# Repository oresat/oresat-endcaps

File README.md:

# "End Cap" PCBs for OreSat

These are the "end cap" PCBs that attach to the +Z and -Z ends of the satellites. Mostly these are to protect the end cards from "space", as well as to hold the magnetometers (two per end cap) as far as away from ferrous stuff as possible. It's also a good place for backup antennas, specifically patch antennas (S band and GPS L1).

## Features

- Cutouts for deployable antennas
- Double magnetometers.
- Single vertical 10mm tall 1.27 mm connector that plugs into the "end card" card.
    - On the End Cap:  Harwin M55-6001242R 12 pin female vertical connector 
    - On the End Card below: Harwin M55-7011242R 12 pin male vertical connector
- No available RF connectors.

## LICENSE

Copyright the Portland State Aerospace Society, 2024.

This source describes Open Hardware that is licensed under CERN-OHL-S v2, or any later version.

You may redistribute and modify this source and make products using it under the terms of the CERN-OHL-S v2 (https://ohwr.org/cern_ohl_s_v2.txt).

This source is distributed WITHOUT ANY EXPRESS OR IMPLIED WARRANTY, INCLUDING OF MERCHANTABILITY, SATISFACTORY QUALITY AND FITNESS FOR A PARTICULAR PURPOSE. Please see the CERN-OHL-S v2 for applicable conditions.

Source location: <https://github.com/oresat/>

As per CERN-OHL-S v2 section 4, should You produce hardware based on this source, You must where practicable maintain the Source Location visible on the external case of the Gizmo or other products you make using this source.

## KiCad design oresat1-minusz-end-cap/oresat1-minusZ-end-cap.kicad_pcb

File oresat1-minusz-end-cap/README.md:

---
title: "**OreSat1 -Z End Cap**"
subtitle: |
  **Fabrication and Assembly Information**\
  For build TIME-STAMP
fontsize: 10pt
geometry:
  - margin=0.5in
toc: true
toc-depth: 2
colorlinks: true
urlcolor: blue
---

\newpage

# About this Board

## Board Description

The OreSat1 -Z End Cap is the board that "caps" the -Z end of the OreSat1 satellite. It protects the -Z End Card and also carries two PNI RM3100 magnetometers, as far away from the internal OreSat magnetic noise as possible. 

## Documentation Links

- End cap hardware Git repository: <https://github.com/oresat/oresat-endcap>
- **TODO:** End Cap Design Notes + Design Review Notes

## Documentation Files

| Filename                        | Notes                                    |
| ------------------------------- | ---------------------------------------- |
| README.pdf                      | This README file                         |
| PROJECT-NAME-outline.dxf        | Board outline (with holes) in DXF format |
| PROJECT-NAME-pcba.step          | 3D model of PCBA (with components)       |
| PROJECT-NAME-render-bot.jpg     | Render of the top of the 3D model        |
| PROJECT-NAME-render-bot.jpg     | Render of the bottom of the 3D model     |
| PROJECT-NAME-schematic.pdf      | PDF of board schematics                  |

## Contact Information

- Website: <https://www.oresat.org/>
- Email: <oresat@pdx.edu>
- Instagram: @pdxaerospace

## Board Renders

{width=50%}
{width=50%}

\newpage

# Printed Circuit Board (PCB) Fabrication Information

## Board Info

- 4 layer board
- Bounding box is 105.6 x 105.6 mm
- Board thickness is 1.59 mm (0.063 inch)

## Board Requirements

- Design Rules
    - Minimum Trace / Space design rules
       - Outer layers: 0.127 mm (5.0 mil) / 0.127 mm (5.0 mil)
       - Inner layers: 0.127 mm (5.0 mil) / 0.127 mm (5.0 mil)
    - Outer dimension router tolerance: +/- 0.254 mm (10.0 mil)
    - Hole placement tolerance: +/- 0.075 mm (3.0 mil)
    - Inner tab routed slot tolerance: +/- 0.254 mm (10.0 mil)
- Drills
   - Drill Positional Tolerance: 0.051 mm (2.0 mil)
   - Drill Size tolerance: +/- 0.064 mm (2.5 mil)
- Plated/Un-plated holes
  - There are 11 un-plated (NPT) holes
  - PTH minimum diameter: 0.254 mm (10 mil)
  - PTH minimum annulus: 0.102 mm (4 mil) radius
- Outline/Routing
  - Requires a 1.0 mm or smaller diameter routing bit
- Slots
  - There are no slots.
- Cutouts
  - There is one cutout.
- There are 3 fiducials on the top layer and 3 fiducials on the bottom layer.
- Panel tabs ("mouse bites")
   - Card edges must be smooth; no mouse bites or other intrusions into the card outline.
   - If external mouse bites are required, minimize and customer will remove by hand before assembly.
- If not otherwise specified, build to IPC 6012 Class 2 or better.

## Materials

- No controlled impedance.
- Outer layers must be 1 oz Copper, inner layers can be 0.5 or 1.0 oz Copper.
- Isola FR408HR or material recommended.
- Board Surface treatment should be ENIG, althogh immersion Silver is acceptable.
- White silkscreen on top and bottom surface
- Taiyo PSR-4000 or equivalent soldermask on top and bottom, no requirements for color.

## Suggested Stack Up

| Layer         | Thickness           | Notes                                        |
|---------------|---------------------|----------------------------------------------|
| Top Copper    | 0.043 mm /  1.7 mil |  Layer 1 foil, 1 oz Cu after plating         |
| prepreg       | 0.200 mm /  7.9 mil |  Prepreg - Isola FR408HR 2113                |
| Layer 2       | 0.018 mm /  0.7 mil |  Layer 2 foil, 0.5 oz Cu                     |
| Core          | 0.991 mm /   39 mil |  Core Isola FR408HR                          |
| Layer 3       | 0.018 mm /  0.7 mil |  Layer 3 foil, 0.5 oz Cu                     |
| prepreg       | 0.200 mm /  7.9 mil |  Prepreg - Isola FR408HR 2113                |
| Bottom Copper | 0.043 mm /  1.7 mil |  Layer 4 foil, 1 oz copper after plating     |
| **Total Stackup** | **1.588 mm / 62.5 mil** |                                      |

## Array / Panel Information

- Coordinate with Contract Manufacturer (CM) for optimal size of this panel.
- If no feedback from CM, then produce single boards (no panel).

## Fabrication Files

### IPC-2581 File

| Filename                 | Notes                                   |
| ------------------------ | --------------------------------------- |
| PROJECT-NAME-ipc2581.xml | IPC-2581 board information file         |

### Legacy PCB Files

| Filename                      | Notes                                         |
| ------------------------------| --------------------------------------------- |
| PROJECT-NAME-Edge_Cuts.gbr    | RS274X file for the dimension (outline) layer |
| PROJECT-NAME-F_Silkscreen.gbr | RS274X file for the top silkscreen            |
| PROJECT-NAME-F_Mask.gbr       | RS274X file for the top soldermask            |
| PROJECT-NAME-F_Cu.gbr         | RS274X file for the top copper layer          |
| PROJECT-NAME-In1_Cu.gbr       | RS274X file for the layer 2 copper            |
| PROJECT-NAME-In2_Cu.gbr       | RS274X file for the layer 3 copper            |
| PROJECT-NAME-B_Cu.gbr         | RS274X file for the bottom copper layer       |
| PROJECT-NAME-B_Mask.gbr       | RS274X file for the bottom soldermask         |
| PROJECT-NAME-B_Silkscreen.gbr | RS274X file for the bottom silkscreen         |
| PROJECT-NAME-NPTH.drl         | Excellon file for non-plated through holes    |
| PROJECT-NAME-PTH.drl          | Excellon file for plated through holes        | 

\newpage

# Printed Circuit Board Assembly (PCBA) Information

## Assembly Info

- There are components on the top and bottom side of the board.
- This PCBA is mostly surface mount (SMT).

## Assembly Requirements

- Assemble to IPC Class 2 or better
- Bake components that are not moisture sealed to appropriate levels as required.
- Solder paste MUST be leaded.
- Aqueous flux and wash strongly preferred.
   - Clean to NASA Standard "Visibly Clean (VC)": No particles or residues are visible to the naked eye.
- No conformal coating.
- Ship in antistatic protective bag

## Component Specific Assembly Information

- No specific requirements.

## Assembly Files

### IPC-2581 File

| Filename                 | Notes                           |
| ------------------------ | ------------------------------- |
| PROJECT-NAME-ipc2581.xml | IPC-2581 board information file |

### Bill of Materials (BOM)

| Filename             | Description                            |
| -------------------- | -------------------------------------- |
| PROJECT-NAME-bom.csv | BOM in Comma Separated Variable format |

### Solder Paste Stencils

| Filename                 | Notes                                            |
| ------------------------ | ------------------------------------------------ |
| PROJECT-NAME-B_Paste.gbr | RS274X file for top/front solder paste stencil   |
| PROJECT-NAME-F_Paste.gbr | RS274X file for bottom/back solder paste stencil |

### Mounting/Placement Location

| Filename            | Description                                 |
| ------------------- | ------------------------------------------- |
| PROJECT-NAME-3u.pos | Pick and place locations for components     |

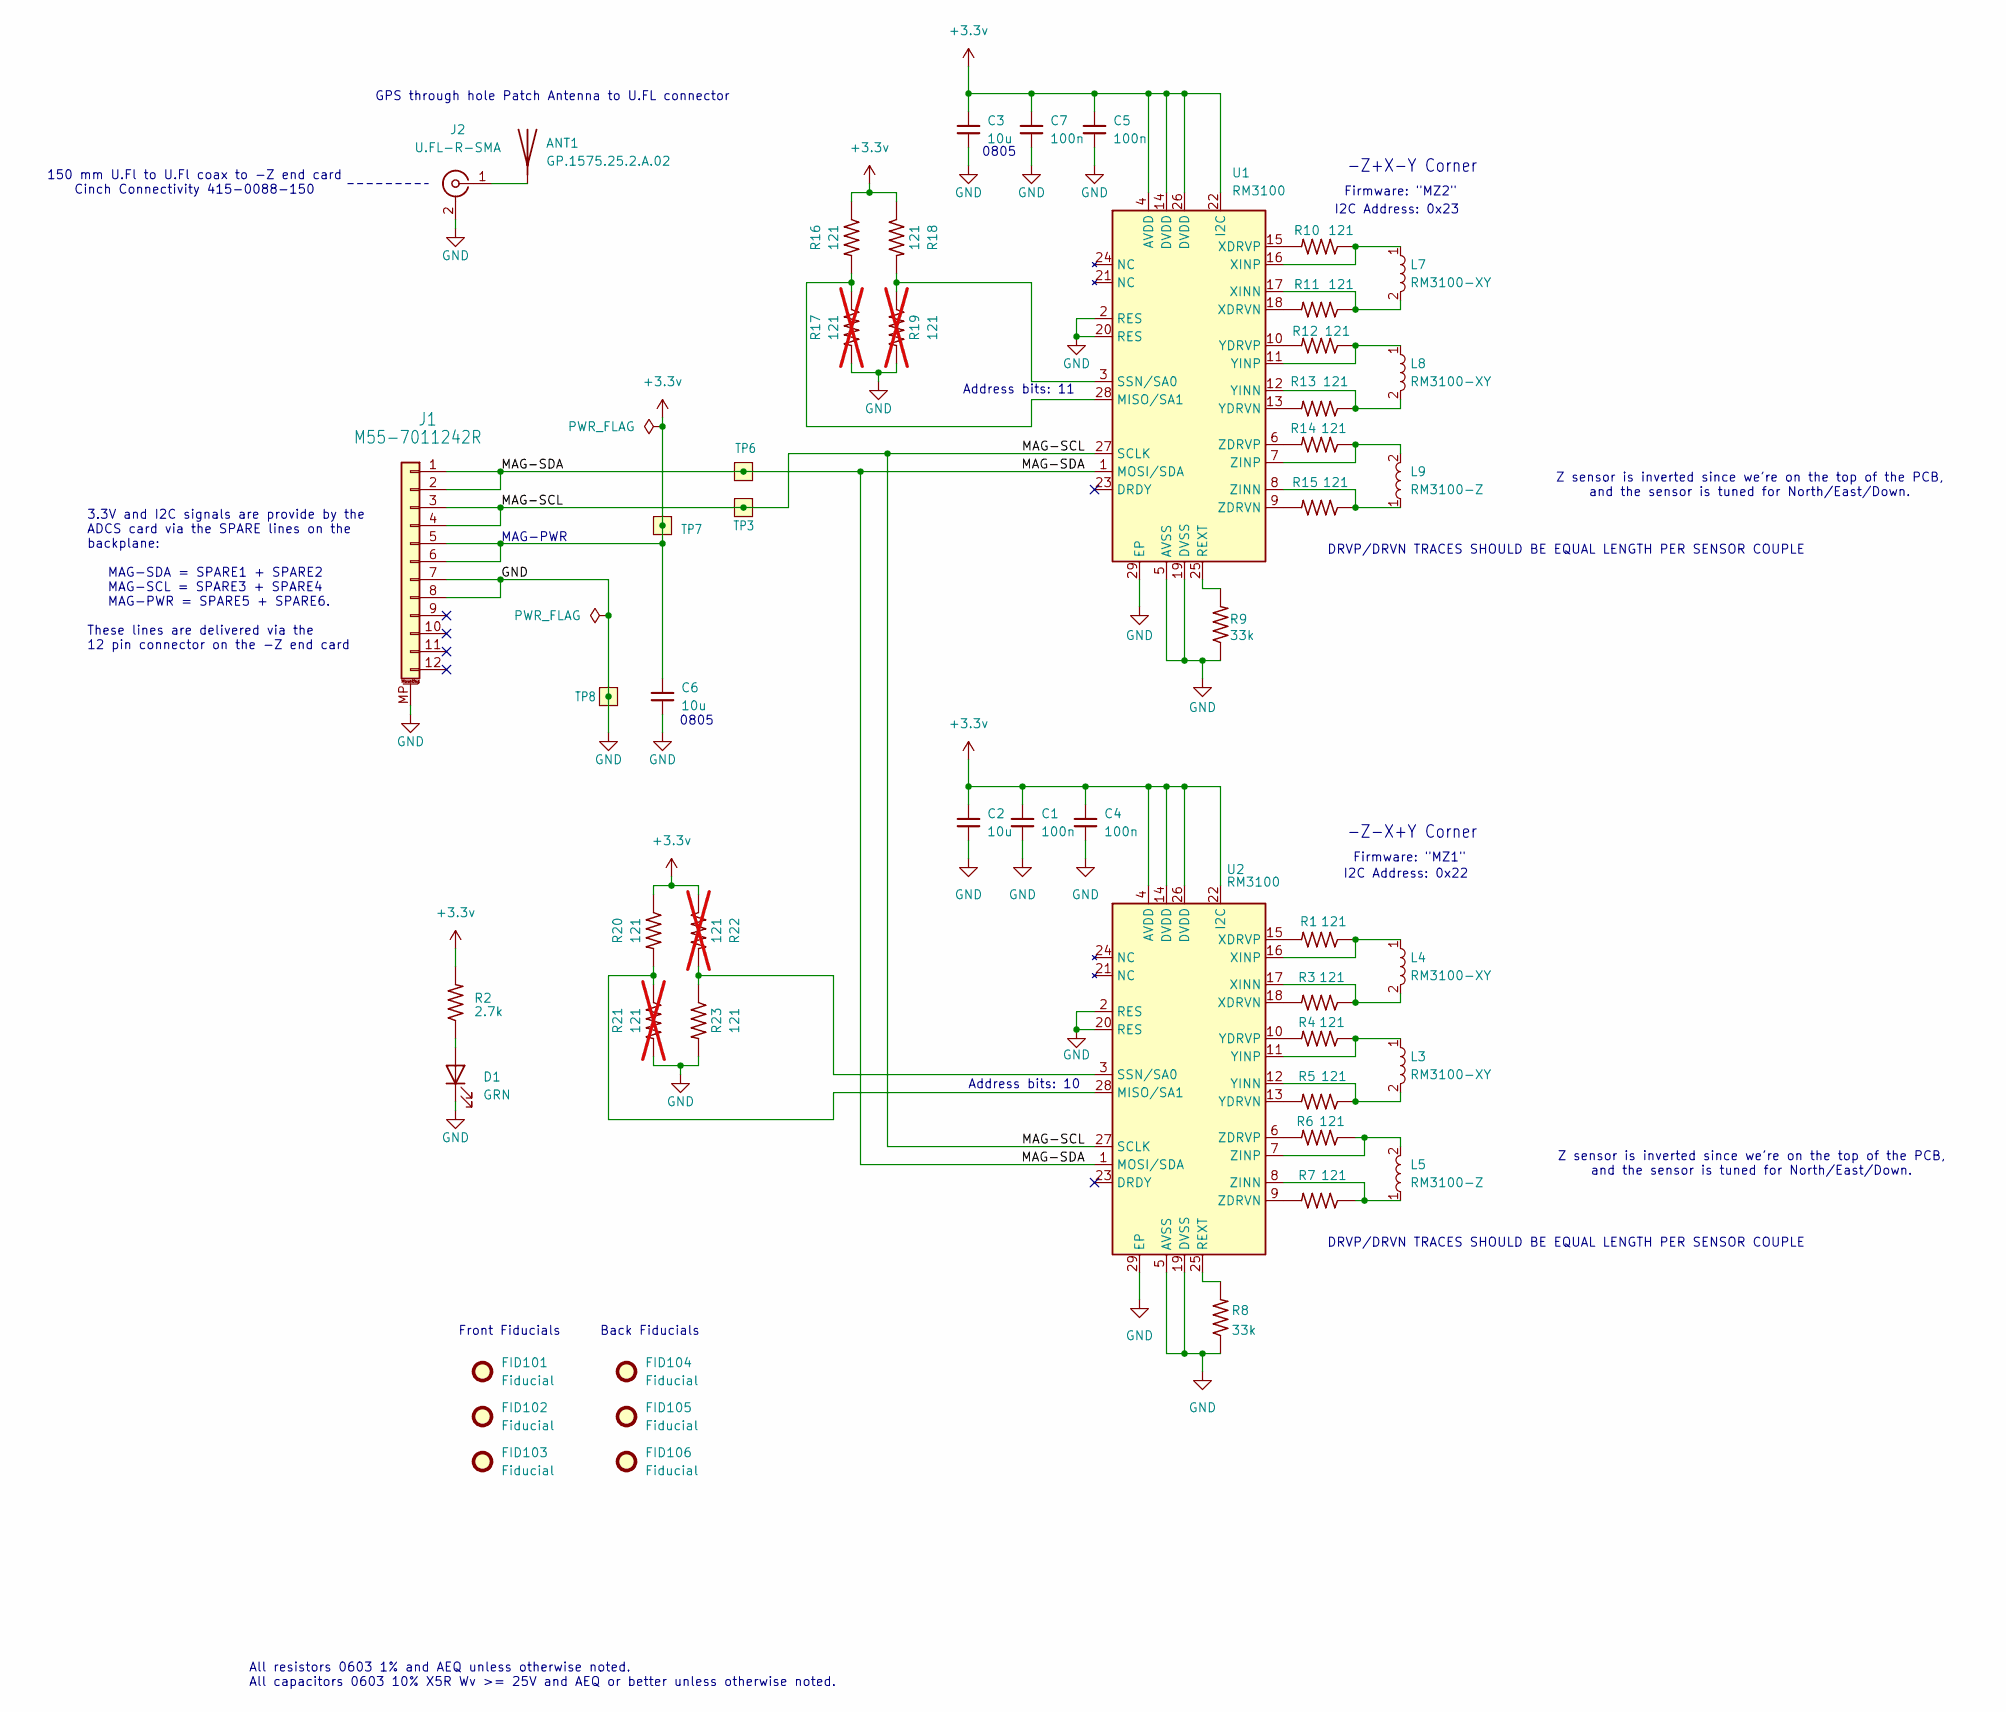
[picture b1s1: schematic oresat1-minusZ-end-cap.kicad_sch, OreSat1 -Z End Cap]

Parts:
ANT1: GP.1575.25.2.A.02; Taoglas-GPS-Patch-Antenna; MPN GP.1575.25.2.A.02
C1, C4, C5, C7: 100n; 0603-C-NOSILK; MPN C0603C104K5RACAUTO
C2, C3, C6: 10u; 0805-C-NOSILK; MPN GRT21BC71E106KE13K
D1: GRN; 0603-C-NOSILK; MPN 150060GS75000
FID101, FID102, FID103, FID104, FID105, FID106: Fiducial; Fiducial_1mm_Mask2mm
J1: M55-7011242R; J-Harwin-M55-7XX1242R; MPN M55-7011242R
J2: U.FL-R-SMA; U.FL_Hirose_U.FL-R-SMT-1_Vertical; MPN U.FL-R-SMT-1(10)
L3, L4, L7, L8: RM3100-XY; RM3100 SEN-XY-f; MFR PNI Sensors
L5, L9: RM3100-Z; RM3100 SEN-Z-f; MFR PNI Sensors
R1, R3, R4, R5, R6, R7, R10, R11, R12, R13, R14, R15, R16, R18, R20, R23: 121; 0603-C-NOSILK; MPN RMCF0603FT121R
R2: 2.7k; 0603-C-NOSILK; MPN RMCF0603FT2K70
R8, R9: 33k; 0603-C-NOSILK; MPN RMCF0603FT33K0
R17, R19, R21, R22: 121; 0603-C-NOSILK; MPN RMCF0603FT121R; not fitted
TP3, TP6, TP7, TP8: Test-Point; TestPoint-0.75mm-th; MPN N/A
U1, U2: RM3100; U-PNI-RM3100-IC; MFR PNI Sensors

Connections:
+3.3v: C1.1, C2.1, C3.1, C4.1, C5.1, C6.1, C7.1, J1.5, J1.6, R2.2, R16.1, R18.1, R20.1, R22.1, TP7.1 (1_1), U1.4 (AVDD), U1.14 (DVDD), U1.22 (I2C), U1.26 (DVDD), U2.4 (AVDD), U2.14 (DVDD), U2.22 (I2C), U2.26 (DVDD)
/MAG-SCL: J1.3, J1.4, TP3.1 (1_1), U1.27 (SCLK), U2.27 (SCLK)
/MAG-SDA: J1.1, J1.2, TP6.1 (1_1), U1.1 (MOSI/SDA), U2.1 (MOSI/SDA)
GND: C1.2, C2.2, C3.2, C4.2, C5.2, C6.2, C7.2, D1.1 (K), J1.7, J1.8, J1.MP (MountPin), J2.2 (Ext), R8.1, R9.1, R17.2, R19.2, R21.2, R23.2, TP8.1 (1_1), U1.2 (RES), U1.5 (AVSS), U1.19 (DVSS), U1.20 (RES), U1.29 (EP), U2.2 (RES), U2.5 (AVSS), U2.19 (DVSS), U2.20 (RES), U2.29 (EP)
unnamed: ANT1.1 (A_1), J2.1 (In)
unnamed: D1.2 (A), R2.1
unnamed: R16.2, R17.1, U1.28 (MISO/SA1)
unnamed: R9.2, U1.25 (REXT)
unnamed: R18.2, R19.1, U1.3 (SSN/SA0)
unnamed: R11.2, U1.18 (XDRVN)
unnamed: R10.2, U1.15 (XDRVP)
unnamed: L7.2, R11.1, U1.17 (XINN)
unnamed: L7.1, R10.1, U1.16 (XINP)
unnamed: R13.2, U1.13 (YDRVN)
unnamed: R12.2, U1.10 (YDRVP)
unnamed: L8.2, R13.1, U1.12 (YINN)
unnamed: L8.1, R12.1, U1.11 (YINP)
unnamed: R15.2, U1.9 (ZDRVN)
unnamed: R14.2, U1.6 (ZDRVP)
unnamed: L9.1, R15.1, U1.8 (ZINN)
unnamed: L9.2, R14.1, U1.7 (ZINP)
unnamed: R20.2, R21.1, U2.28 (MISO/SA1)
unnamed: R8.2, U2.25 (REXT)
unnamed: R22.2, R23.1, U2.3 (SSN/SA0)
unnamed: R3.2, U2.18 (XDRVN)
unnamed: R1.2, U2.15 (XDRVP)
unnamed: L4.2, R3.1, U2.17 (XINN)
unnamed: L4.1, R1.1, U2.16 (XINP)
unnamed: R5.2, U2.13 (YDRVN)
unnamed: R4.2, U2.10 (YDRVP)
unnamed: L3.2, R5.1, U2.12 (YINN)
unnamed: L3.1, R4.1, U2.11 (YINP)
unnamed: R7.2, U2.9 (ZDRVN)
unnamed: R6.2, U2.6 (ZDRVP)
unnamed: L5.1, R7.1, U2.8 (ZINN)
unnamed: L5.2, R6.1, U2.7 (ZINP)

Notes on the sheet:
Back Fiducials
0805
GPS through hole Patch Antenna to U.FL connector
Firmware: "MZ2"
-Z+X-Y Corner
Z sensor is inverted since we're on the top of the PCB, and the sensor is tuned for North/East/Down.
I2C Address: 0x22
DRVP/DRVN TRACES SHOULD BE EQUAL LENGTH PER SENSOR COUPLE
Address bits: 10
-Z-X+Y Corner
Front Fiducials
MAG-PWR
Firmware: "MZ1"
3.3V and I2C signals are provide by the ADCS card via the SPARE lines on the backplane: MAG-SDA = SPARE1 + SPARE2 MAG-SCL = SPARE3 + SPARE4 MAG-PWR = SPARE5 + SPARE6. These lines are delivered via the 12 pin connector on the -Z end card
Address bits: 11
150 mm U.Fl to U.Fl coax to -Z end card Cinch Connectivity 415-0088-150
All resistors 0603 1% and AEQ unless otherwise noted. All capacitors 0603 10% X5R Wv >= 25V and AEQ or better unless otherwise noted.
I2C Address: 0x23

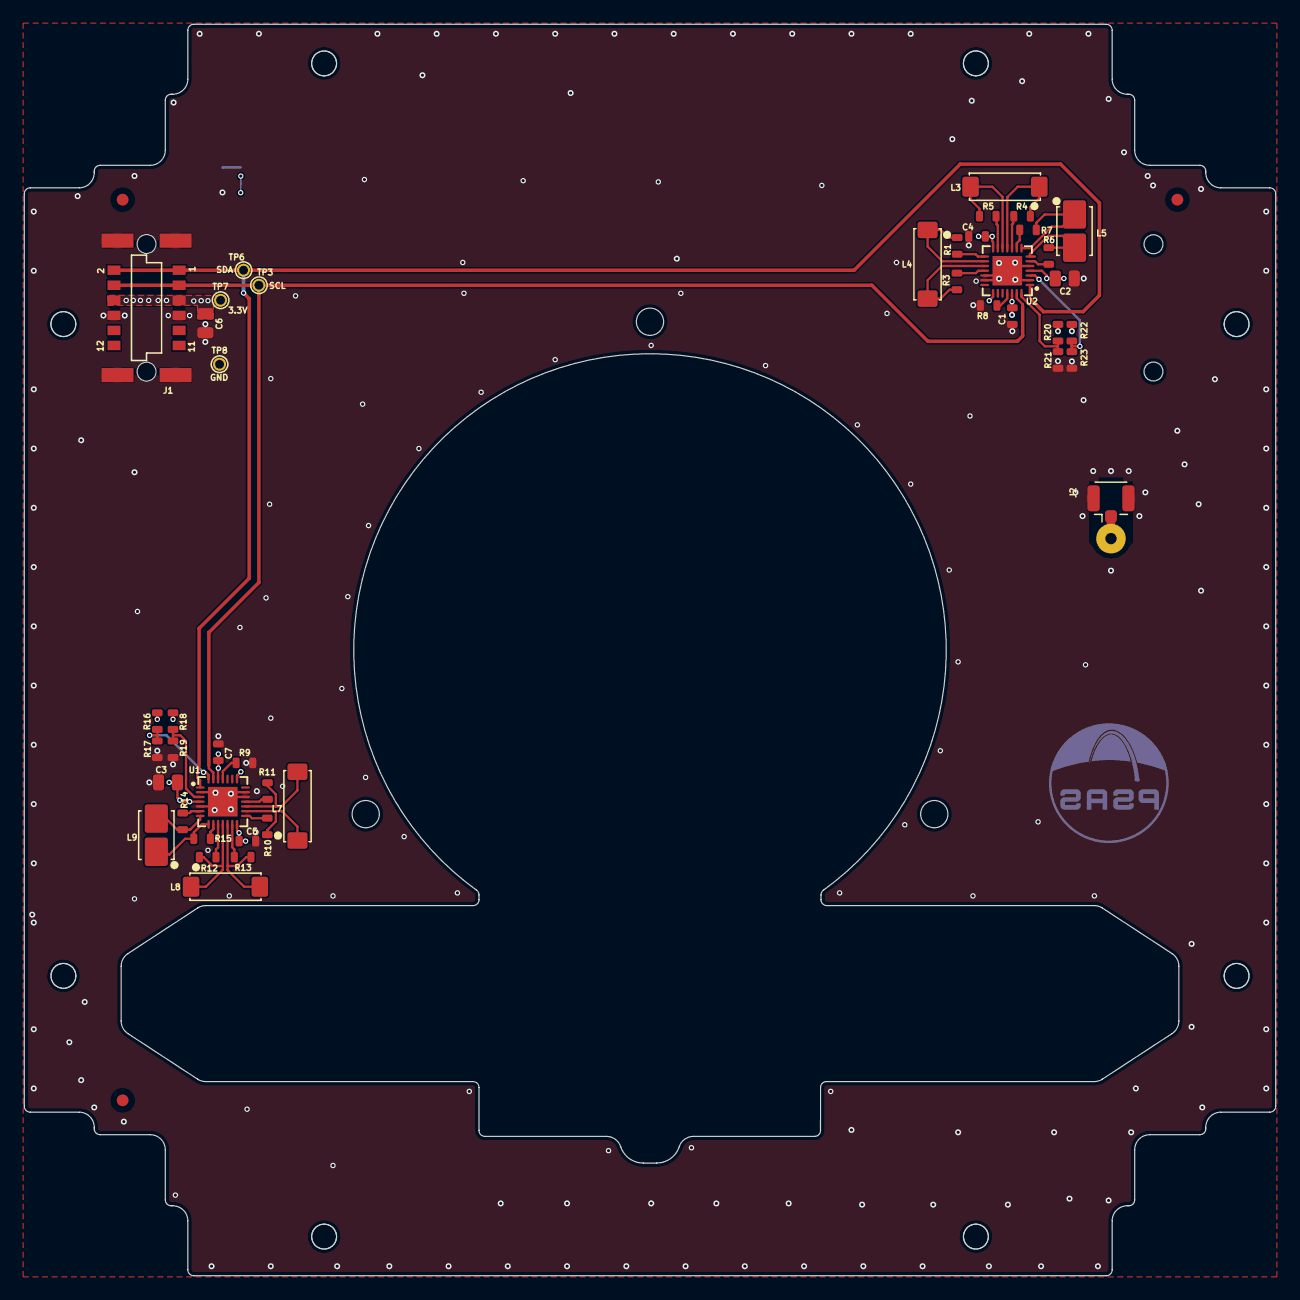
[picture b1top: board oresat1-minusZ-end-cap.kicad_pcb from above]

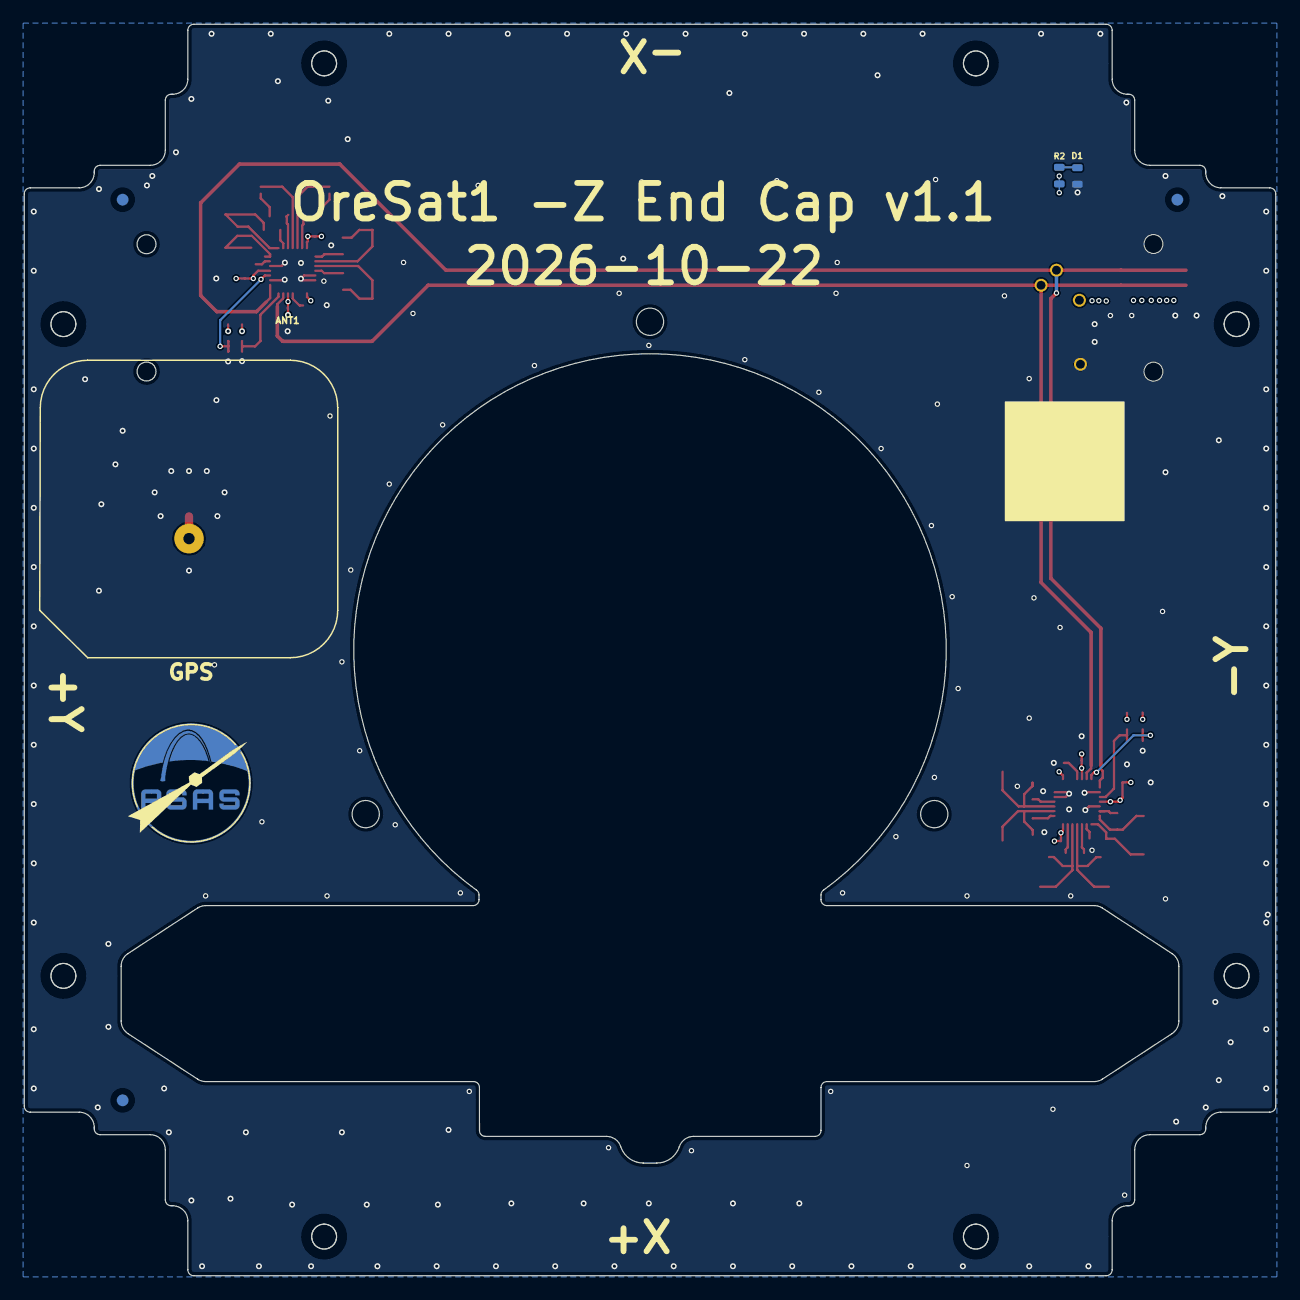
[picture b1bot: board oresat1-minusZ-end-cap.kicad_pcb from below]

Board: 4 copper layers, 105.6 x 105.6 mm, 53 parts (7 on the bottom side), 36 nets.

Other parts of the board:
LOGO1: PSAS_LOGO_10X10

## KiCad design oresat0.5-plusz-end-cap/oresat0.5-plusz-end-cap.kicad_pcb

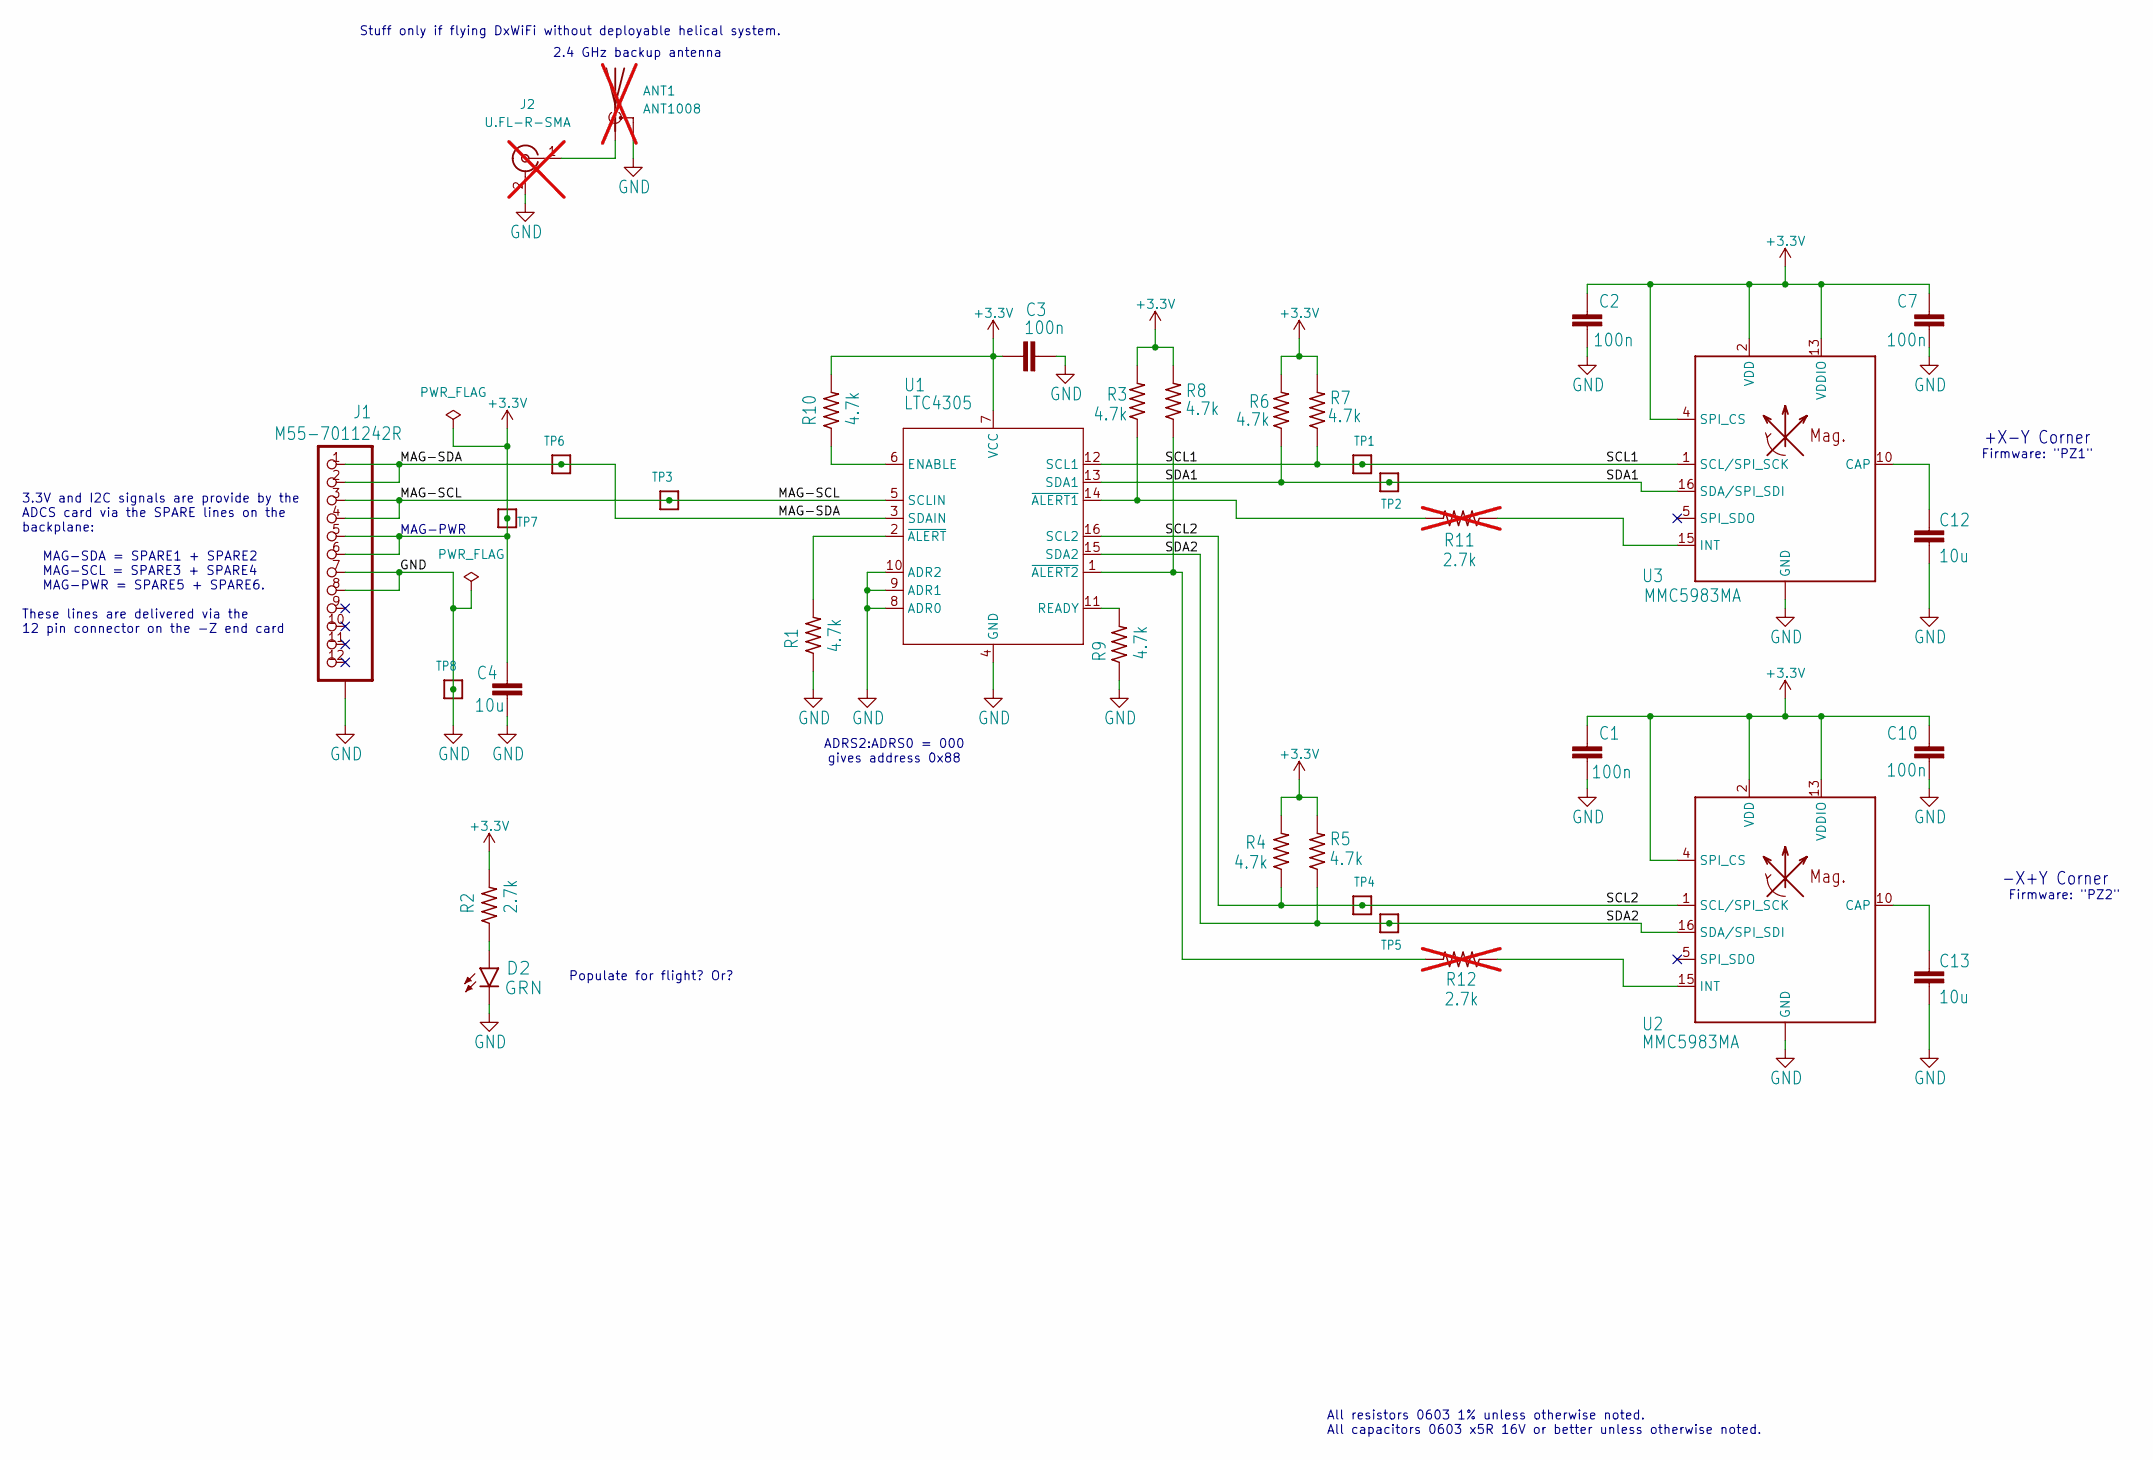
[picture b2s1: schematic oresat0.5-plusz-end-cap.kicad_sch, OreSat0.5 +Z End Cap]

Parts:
ANT1: ANT1008; RFMi-ANT1008-S-Band-Patch; MPN ANT1008; not fitted
C1, C2, C3, C7, C10: 100n; .0603-B-NOSILK; MPN TMK107BJ104KAHT
C4, C12, C13: 10u; .0603-B-NOSILK; MPN GRT188R61C106KE13D
D2: GRN; LED-0603; MPN 150060GS75000
J1: M55-7011242R; HARWIN-M55-70X1242R; MPN M55-7011242R
J2: U.FL-R-SMA; U.FL_Hirose_U.FL-R-SMT-1_Vertical; MPN U.FL-R-SMT-1(10); not fitted
R1, R3, R4, R5, R6, R7, R8, R9, R10: 4.7k; .0603-B-NOSILK; MPN RMCF0603FT4K70
R2: 2.7k; .0603-B-NOSILK; MPN RMCF0603FT2K70
R11, R12: 2.7k; .0603-B-NOSILK; MPN RMCF0603FT2K70; not fitted
TP1, TP2, TP3, TP4, TP5, TP6, TP7, TP8: TEST-POINT-LARGE-SQUARE; TestPoint-0.75mm-th; MPN N/A
U1: LTC4305; 16-SSOP; MPN LTC4305IGN#PBF
U2, U3: MMC5983MA; LGA-16(3X3); MPN MMC5883MA

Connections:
+3.3V: C1.1, C2.1, C3.1, C4.1, C7.1, C10.1, J1.5, J1.6, R2.2, R3.2, R4.2, R5.2, R6.2, R7.2, R8.2, R10.2, TP7.1, U1.7 (VCC), U2.2 (VDD), U2.4 (SPI_CS), U2.13 (VDDIO), U3.2 (VDD), U3.4 (SPI_CS), U3.13 (VDDIO)
/MAG-SCL: J1.3, J1.4, TP3.1, U1.5 (SCLIN)
/MAG-SDA: J1.1, J1.2, TP6.1, U1.3 (SDAIN)
/SCL1: R7.1, TP1.1, U1.12 (SCL1), U3.1 (SCL/SPI_SCK)
/SCL2: R4.1, TP4.1, U1.16 (SCL2), U2.1 (SCL/SPI_SCK)
/SDA1: R6.1, TP2.1, U1.13 (SDA1), U3.16 (SDA/SPI_SDI)
/SDA2: R5.1, TP5.1, U1.15 (SDA2), U2.16 (SDA/SPI_SDI)
GND: ANT1.2 (Shield), C1.2, C2.2, C3.2, C4.2, C7.2, C10.2, C12.2, C13.2, D2.C, J1.7, J1.8, J1.P$1 (SHIELDS), J1.P$2 (SHIELDS), J1.P$3 (SHIELDS), J1.P$4 (SHIELDS), J2.2 (Ext), R1.1, R9.1, TP8.1, U1.4 (GND), U1.8 (ADR0), U1.9 (ADR1), U1.10 (ADR2), U2.9 (GND), U2.11 (GND), U3.9 (GND), U3.11 (GND)
unnamed: ANT1.1 (A), J2.1 (In)
unnamed: D2.A, R2.1
unnamed: R10.1, U1.6 (ENABLE)
unnamed: R9.2, U1.11 (READY)
unnamed: R3.1, R11.2, U1.14 (~ALERT1)
unnamed: R8.1, R12.2, U1.1 (~ALERT2)
unnamed: R1.2, U1.2 (~ALERT)
unnamed: C13.1, U2.10 (CAP)
unnamed: R12.1, U2.15 (INT)
unnamed: C12.1, U3.10 (CAP)
unnamed: R11.1, U3.15 (INT)

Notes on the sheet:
-X+Y Corner
MAG-PWR
All resistors 0603 1% unless otherwise noted. All capacitors 0603 x5R 16V or better unless otherwise noted.
Stuff only if flying DxWiFi without deployable helical system.
Populate for flight? Or?
Firmware: "PZ2"
+X-Y Corner
ADRS2:ADRS0 = 000 gives address 0x88
Firmware: "PZ1"
3.3V and I2C signals are provide by the ADCS card via the SPARE lines on the backplane: MAG-SDA = SPARE1 + SPARE2 MAG-SCL = SPARE3 + SPARE4 MAG-PWR = SPARE5 + SPARE6. These lines are delivered via the 12 pin connector on the -Z end card
2.4 GHz backup antenna

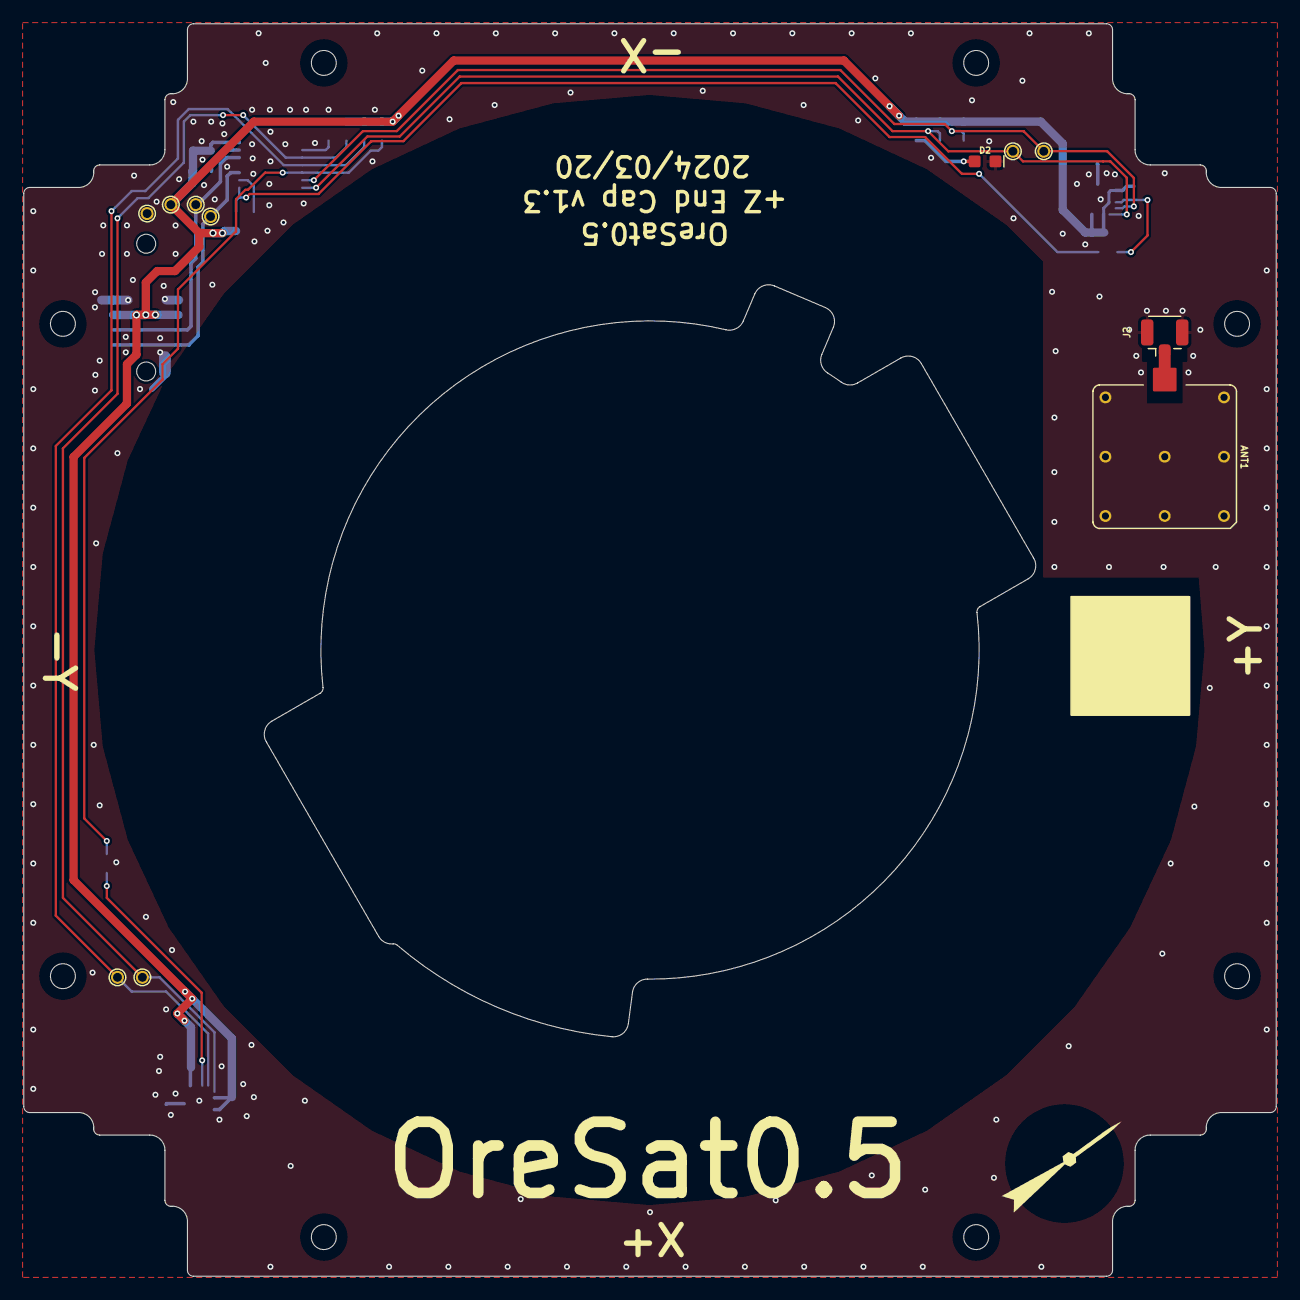
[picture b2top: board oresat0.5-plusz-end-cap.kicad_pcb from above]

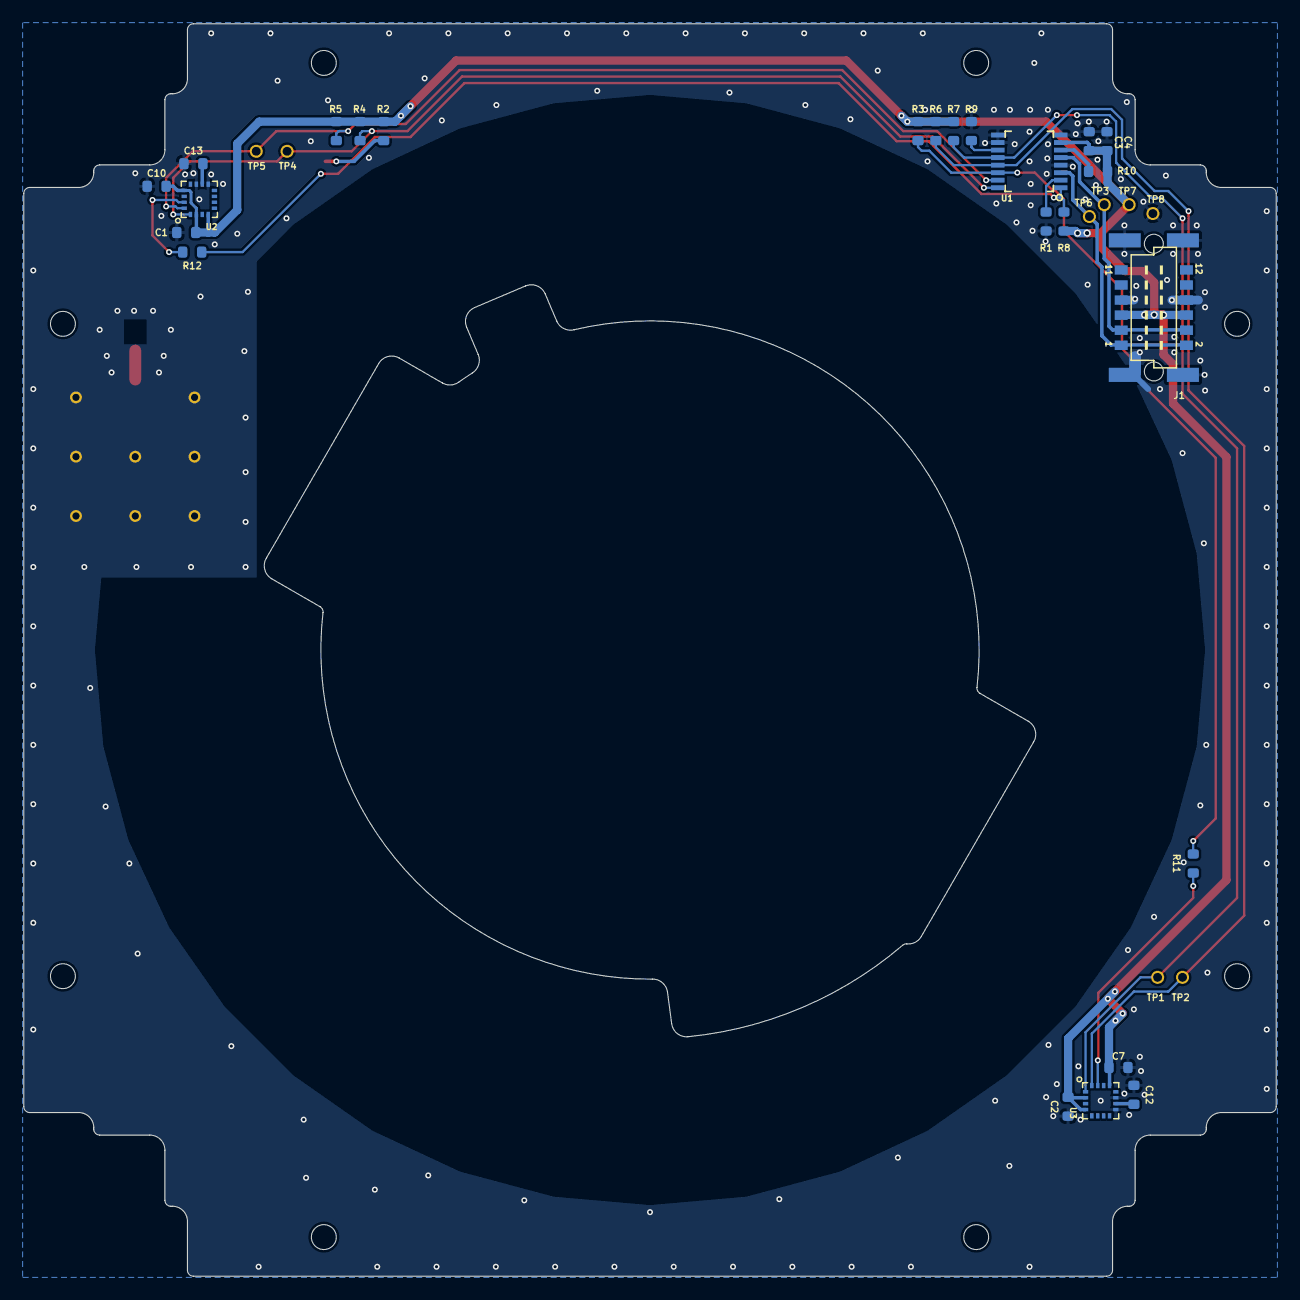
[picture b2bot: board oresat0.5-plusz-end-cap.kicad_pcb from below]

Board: 2 copper layers, 105.6 x 105.6 mm, 44 parts (24 on the bottom side), 19 nets.

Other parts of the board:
@HOLE4, @HOLE4#2, @HOLE4#3, @HOLE4#4, @HOLE4#5, @HOLE4#6, @HOLE4#7, @HOLE4#8: MountingHole_2.1mm
LOGO1: PSAS_LOGO_10X10

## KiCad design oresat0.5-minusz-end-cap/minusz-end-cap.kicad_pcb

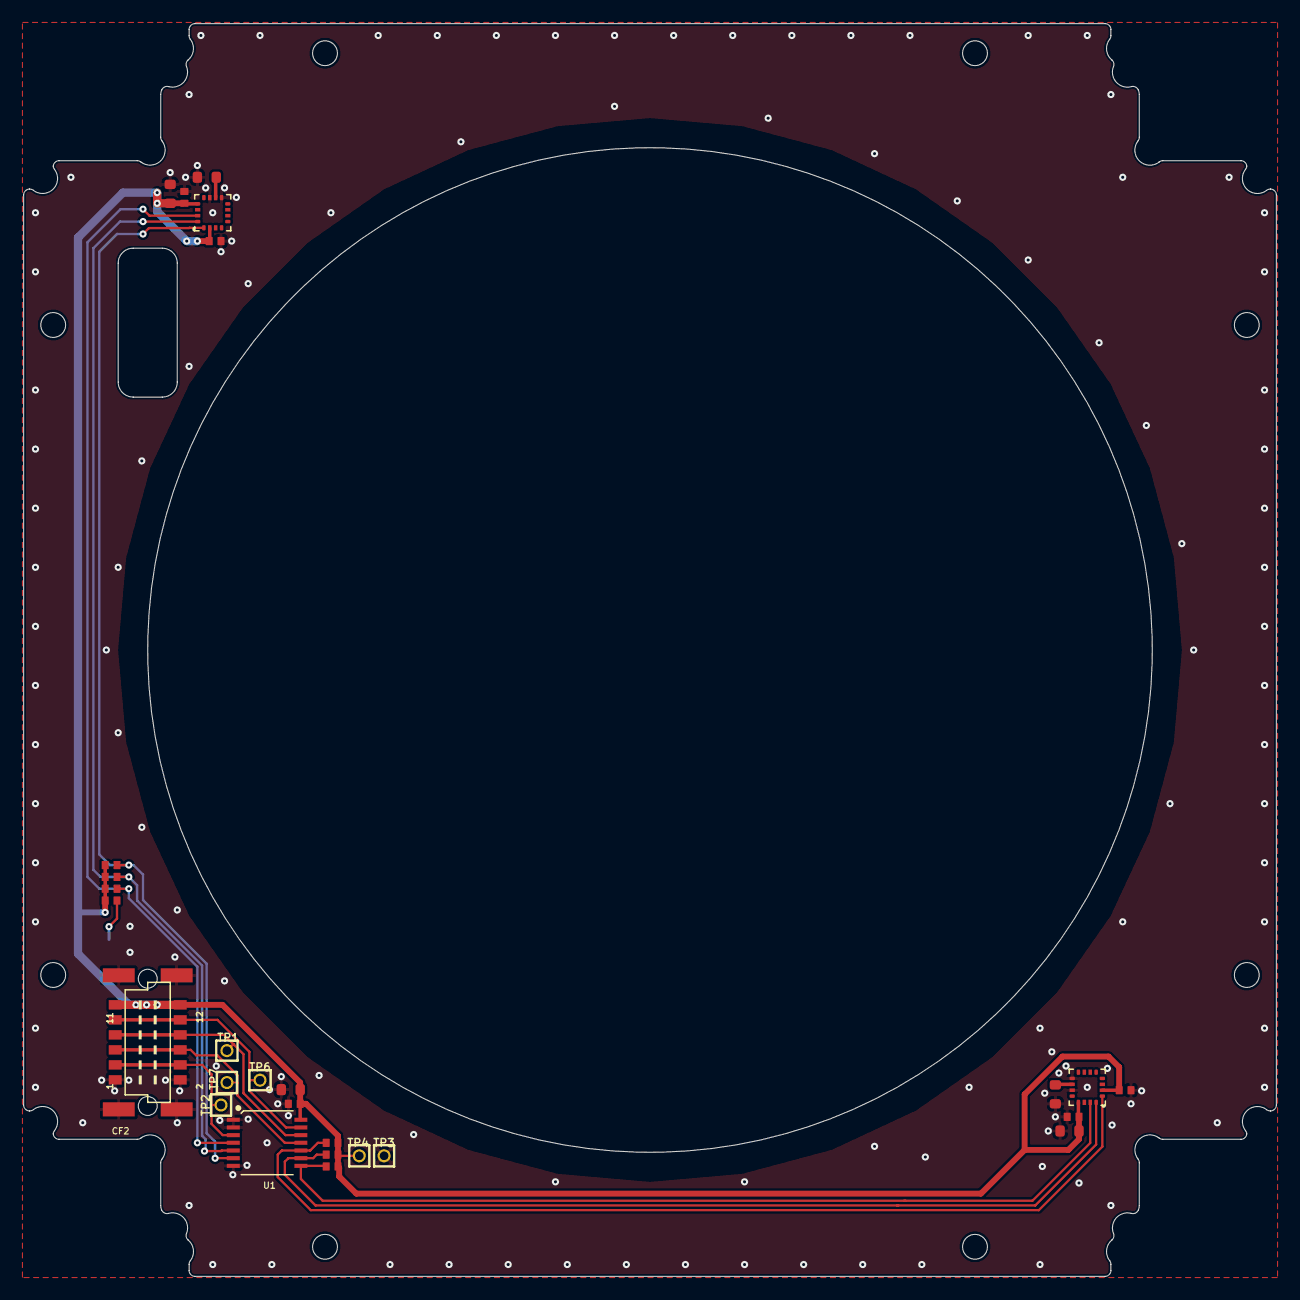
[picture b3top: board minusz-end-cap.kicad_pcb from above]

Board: 2 copper layers, 106.0 x 106.0 mm, 36 parts (1 on the bottom side), 15 nets.

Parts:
@HOLE0, @HOLE1, @HOLE2, @HOLE3, @HOLE4, @HOLE5, @HOLE6, @HOLE7: (no value)
C1, C2, C3, C7, C10: 100n; .0402-B-NOSILK
C4, C12, C13: 10u; .0603-B-NOSILK
C15, C19: 4.7u; .0603-B-NOSILK
CF2: J-HARWIN-M55-70X1242R; HARWIN-M55-70X1242R
D2: GREEN; LED-0603
R1, R3, R4, R5, R6, R7: 4.7k; .0402-B-NOSILK
R2: 2.7k; .0402-B-NOSILK
TP1, TP2, TP3, TP4, TP6, TP7: TEST-POINT; 2MM-TEST-POINT
U1: TCA9543A-PW; TSSOP14-0.65-5.4X4.4MM
U3, U4: HMC5883L; QLGA-16(3X3)

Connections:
3.3V: C1.1, C2.1, C3.1, C4.1, C7.1, C10.1, C15.1, C19.1, CF2.11, CF2.12, R1.2, R2.2, R3.2, R4.2, R5.2, R6.2, R7.2, TP4.1, U1.14, U3.2, U3.13, U4.2, U4.13
GND: C1.2, C2.2, C3.2, C4.2, C7.2, C10.2, C12.2, C13.2, C15.2, C19.2, CF2.1, CF2.2, CF2.P$1, CF2.P$2, CF2.P$3, CF2.P$4, D2.C, TP3.1, U1.1, U1.2, U1.7, U3.9, U3.11, U4.9, U4.11
I2C-SCL: CF2.7, CF2.8, TP1.1, U1.12
I2C-SDA: CF2.9, CF2.10, TP6.1, U1.13
I2C-~INT: CF2.5, CF2.6, TP7.1, U1.11
unnamed: C12.1, U3.10
unnamed: C13.1, U4.10
unnamed: D2.A, R2.1
SC1: R7.1, U1.10, U3.1
SCL0: R4.1, U1.6, U4.1
SD1: R6.1, U1.9, U3.16
SDA0: R5.1, U1.5, U4.16
~I2C-RESET: CF2.3, CF2.4, TP2.1, U1.3
~INT0: R1.1, U1.4, U4.15
~INT1: R3.1, U1.8, U3.15
